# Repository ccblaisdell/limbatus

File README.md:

# limbatus

A 36-key wireless monoblock ergonomic keyboard derived from Dimetrodon.

## Current status
- Ships as a **36-key** layout (3 thumb keys per side).
- Matrix is organized as a XIAO BLE-compatible logical `6 x 6` scan.
- `NFC1` is reserved for matrix use and must be configured as GPIO in firmware.
- The thumb cluster's anchor/shift/splay values match Dimetrodon's thumb
  cluster exactly (same fan shape, ported into limbatus's mirrored monoblock
  frame).

## Latest PCB Images
- Top view: https://ccblaisdell.github.io/limbatus/limbatus-top.png
- Bottom view: https://ccblaisdell.github.io/limbatus/limbatus-bottom.png

## Build
1. Install dependencies:
   - `npm install`
2. Generate artifacts:
   - `make build`

For hand-assembly (soldering and case), see [`BUILD.md`](BUILD.md). Parts list is in [`BOM.md`](BOM.md).

## Firmware
Runs [ZMK](https://zmk.dev) as a single (non-split) XIAO BLE image. The config,
keymaps, pin map, and build/flash notes live in [`config/`](config/README.md);
CI builds the `limbatus` shield and uploads a `.uf2` artifact.

Default keymap (rendered by [keymap-drawer](https://github.com/caksoylar/keymap-drawer)):

## Verify Ergogen Changes
Run this whenever you change `ergogen/config.yaml`.

1. Build:
   - `make build`
2. Verify generated artifacts exist:
   - `ls outlines`
   - `ls pcbs`
3. Check what changed:
   - `git status --short`
4. In KiCad, open the generated board and confirm:
   - no missing footprints
   - 36 keys present
   - MCU footprint placement still valid
   - no obvious overlap/regression in thumb cluster or center bridge

## Keyboard References
- https://github.com/ceoloide/corney-island for its GitHub Actions and workflows.
- https://github.com/ccblaisdell/dimetrodon for your previous keyboard iteration.

## Notes
- Target MCU is XIAO BLE nRF52840.
- Matrix pin map target: `P0..P5` for columns, `P6..P10` plus `NFC1` for rows.
- Includes a dedicated power switch footprint.
- No JST footprint; battery uses two direct-solder SMD pads (`local/battery_pads_solder`).
- No external reset switch footprint; rely on the onboard XIAO reset button.
- The current code-generated case approach is documented in `case/README.md` and is intended to use Ergogen DXFs plus an OpenSCAD/FreeCAD export flow.

## TODO
- Add 3d models for parts where possible
- Implement the code-generated case plan in `case/README.md`
- Design a second case with embedded apple magic trackpad

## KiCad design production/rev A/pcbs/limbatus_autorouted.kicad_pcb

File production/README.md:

# Production artifacts

This directory holds **production bundles**: frozen snapshots of the exact
fabrication artifacts for a specific board revision — the gerbers you actually
order, together with the PCB and outlines they were generated from.

Everything else generated by Ergogen (`outlines/`, `pcbs/`) and by KiBot
(root `gerbers/`) is a **live build product** and is intentionally *not* committed
(see `.gitignore`). `ergogen/config.yaml` is the single source of truth; run
`make build` (or download the CI build artifacts) to regenerate the current
design at any time.

## Layout

```
production/
  rev <version>/                 # e.g. 2026-08-01-jlcpcb
    gerbers/
      limbatus/               # base-board gerbers
      limbatus.zip            # the zip actually uploaded to the fab
      limbatus_autorouted/    # autorouted-board gerbers (if used)
      limbatus_autorouted.zip
    limbatus.kicad_pcb        # the exact PCB the gerbers came from
    outlines/                 # matching board/case outlines
    BOM.csv                   # optional: BOM as ordered
    SOURCE.md                 # provenance: source commit, date, fab, order id
```

A bundle is **immutable** once committed. It is guaranteed internally consistent
(gerbers ⇄ PCB ⇄ outlines all from one build), which is the property root-level
live outputs cannot promise as the design evolves.

## Cutting a new production bundle

Bundles are created and committed **by hand** — nothing in CI writes here.
When you are ready to place an order:

1. Regenerate from the commit you intend to fab: `make build`, then run the
   KiBot/autoroute steps to produce `gerbers/` (or pull them from the `Build`
   workflow's `kibot-default` artifact for that commit).
2. Copy the artifacts into `production/<order-id>/`:
   - `gerbers/`            → `production/<order-id>/gerbers/`
   - `pcbs/limbatus.kicad_pcb` → `production/<order-id>/limbatus.kicad_pcb`
   - `outlines/`          → `production/<order-id>/outlines/`
3. Write `production/<order-id>/SOURCE.md` recording the source commit, date,
   fab, and order id (copy an existing bundle's `SOURCE.md` as a template).
4. Commit the bundle and tag it: `git tag fab-<order-id> && git push --tags`.

Because `outlines/`, `pcbs/`, and root `gerbers/` are gitignored, use
`git add -f production/<order-id>` — the `production/` path itself is not
ignored, so a normal `git add production/<order-id>` works too.

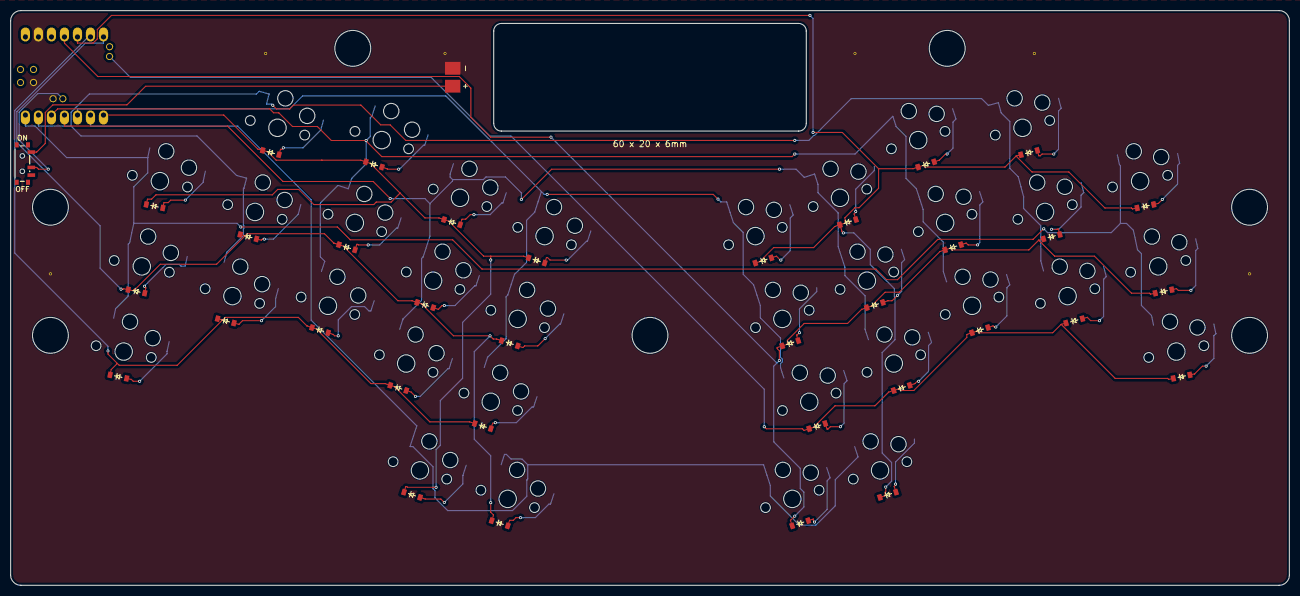
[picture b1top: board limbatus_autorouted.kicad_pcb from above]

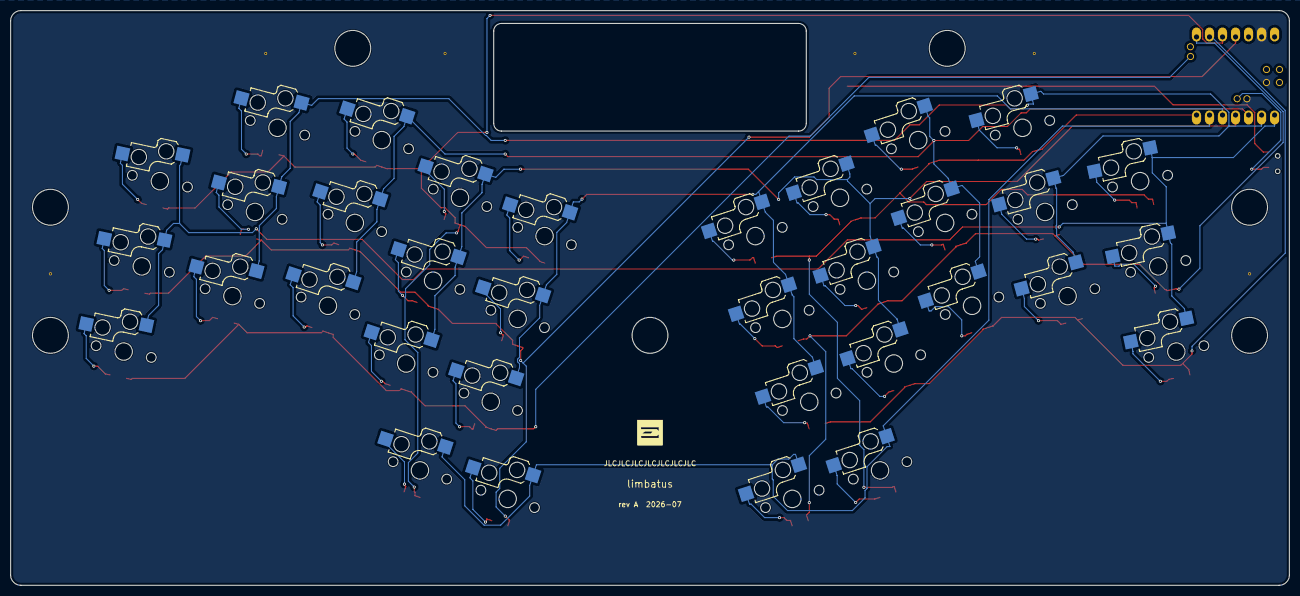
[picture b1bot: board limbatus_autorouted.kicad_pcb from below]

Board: 2 copper layers, 249.5 x 112.1 mm, 85 parts (35 on the bottom side), 49 nets.

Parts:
BAT1: battery_pads_solder
D1, D2, D3, D4, D5, D6, D7, D8, D9, D10, D11, D12, D13, D14, D15, D16, D17, D18, D19, D20, D21, D22, D23, D24, D25, D26, D27, D28, D29, D30, D31, D32, D33, D34: diode_tht_sod123
LOGO1: utility_ergogen_logo
MCU1: XIAO-BLE
MH1, MH2, MH3, MH4, MH5, MH6, MH7: mounting_hole_npth
PWR1: power_switch_smd_side
S1, S2, S3, S4, S5, S6, S7, S8, S9, S10, S11, S12, S13, S14, S15, S16, S17, S18, S19, S20, S21, S22, S23, S24, S25, S26, S27, S28, S29, S30, S31, S32, S33, S34: switch_choc_v1_v2
V1, V2, V3, V4, V5, V6: stitching_via

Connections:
Braw: BAT1.1, PWR1.1
C0: MCU1.1, S1.1, S2.1, S3.1, S18.1, S19.1, S20.1
C1: MCU1.2, S4.1, S5.1, S6.1, S21.1, S22.1, S23.1
C2: MCU1.3, S7.1, S8.1, S9.1, S24.1, S25.1, S26.1
C3: MCU1.4, S10.1, S11.1, S12.1, S27.1, S28.1, S29.1
C4: MCU1.5, S13.1, S14.1, S15.1, S30.1, S31.1, S32.1
C5: MCU1.6, S16.1, S17.1, S33.1, S34.1
GND: BAT1.2, MCU1.13, MCU1.17, MCU1.20, V1.1, V2.1, V3.1, V4.1, V5.1, V6.1
R0: D3.1, D6.1, D9.1, D12.1, D15.1, D16.1, MCU1.7
R1: D2.1, D5.1, D8.1, D11.1, D14.1, D17.1, MCU1.8
R2: D1.1, D4.1, D7.1, D10.1, D13.1, MCU1.9
R3: D20.1, D23.1, D26.1, D29.1, D32.1, D33.1, MCU1.10
R4: D19.1, D22.1, D25.1, D28.1, D31.1, D34.1, MCU1.11
R5: D18.1, D21.1, D24.1, D27.1, D30.1, MCU1.21
RAW: MCU1.19, PWR1.2
SW_left_matrix_inner_bottom: D13.2, S13.2
SW_left_matrix_inner_home: D14.2, S14.2
SW_left_matrix_inner_top: D15.2, S15.2
SW_left_matrix_middle_bottom: D7.2, S7.2
SW_left_matrix_middle_home: D8.2, S8.2
SW_left_matrix_middle_top: D9.2, S9.2
SW_left_matrix_pinky_bottom: D1.2, S1.2
SW_left_matrix_pinky_home: D2.2, S2.2
SW_left_matrix_pinky_top: D3.2, S3.2
SW_left_matrix_pointer_bottom: D10.2, S10.2
SW_left_matrix_pointer_home: D11.2, S11.2
SW_left_matrix_pointer_top: D12.2, S12.2
SW_left_matrix_ring_bottom: D4.2, S4.2
SW_left_matrix_ring_home: D5.2, S5.2
SW_left_matrix_ring_top: D6.2, S6.2
SW_left_thumbs_middle_cluster: D17.2, S17.2
SW_left_thumbs_tucky_cluster: D16.2, S16.2
SW_mirror_left_matrix_inner_bottom: D30.2, S30.2
SW_mirror_left_matrix_inner_home: D31.2, S31.2
SW_mirror_left_matrix_inner_top: D32.2, S32.2
SW_mirror_left_matrix_middle_bottom: D24.2, S24.2
SW_mirror_left_matrix_middle_home: D25.2, S25.2
SW_mirror_left_matrix_middle_top: D26.2, S26.2
SW_mirror_left_matrix_pinky_bottom: D18.2, S18.2
SW_mirror_left_matrix_pinky_home: D19.2, S19.2
SW_mirror_left_matrix_pinky_top: D20.2, S20.2
SW_mirror_left_matrix_pointer_bottom: D27.2, S27.2
SW_mirror_left_matrix_pointer_home: D28.2, S28.2
SW_mirror_left_matrix_pointer_top: D29.2, S29.2
SW_mirror_left_matrix_ring_bottom: D21.2, S21.2
SW_mirror_left_matrix_ring_home: D22.2, S22.2
SW_mirror_left_matrix_ring_top: D23.2, S23.2
SW_mirror_left_thumbs_middle_cluster: D34.2, S34.2
SW_mirror_left_thumbs_tucky_cluster: D33.2, S33.2

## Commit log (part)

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2026-03-02 Add agents config
2026-03-02 Generated an ergogen config
2026-03-02 Set node version
2026-03-02 Initial npm install
2026-03-02 Verification instructions
2026-03-02 Fix skip option error
2026-03-02 Fix mirroring
2026-03-02 Fix spacing
2026-03-02 Rotation, spacing, and remove arc from thumbs
2026-03-02 Fixed rectangular board
2026-03-03 Remove reset button
2026-03-03 Move controller to the board edge
2026-03-03 Remove references to rp2040
2026-03-04 Use ceoloide's choc switch footprint
2026-03-05 Add ceoloide's footprints as git submodule
2026-03-05 Add actual xiao footprint
2026-03-05 Add github workflow
2026-03-05 Add reproducibility check to CI workflow
2026-03-05 Port KiBot action wrappers and add CI KiBot job
2026-03-05 Make KiBot action compatible with generated PCB token
2026-03-05 Deploy KiBot images to GitHub Pages
2026-03-05 Enable Pages setup during workflow deploy
2026-03-05 Grant Pages permissions to KiBot job
2026-03-05 Gate Pages deploy behind ENABLE_PAGES variable
2026-03-05 Run Pages deploy on main without feature flag
2026-03-05 Fix yaml unhappiness
2026-03-05 Add TODOS to readme
2026-03-07 Add published PCB images to README
2026-03-08 Add dimetrodon power switch footprint to Ergogen config
2026-03-08 Bring halves closer together
2026-03-08 Update readme with reference implementations
2026-03-08 Wire DSN autoroute pipeline into CI and update TODOs
2026-03-08 Use default KiBot config for autorouted board outputs
2026-03-09 Add top-side 20x32 battery placement scaffold
2026-03-09 Move xiao to the corner, bigger battery
2026-03-10 Tweak outlines
2026-03-10 Add SMD diodes
2026-03-10 Add case plan, will follow up on it later
2026-03-11 Reference local corney-island repo
2026-03-11 Use NFC1 pin for 6x6 matrix
2026-03-11 Move diodes
2026-03-11 Tweak diode placement a little more
2026-03-11 Prep for the case
2026-03-12 Switch from codex to claude
2026-03-12 Added outlines intended to help with the case
2026-03-14 First pass at a case
2026-06-10 Trying to iterate on the openscad case
2026-06-25 Ignore worktrees
2026-06-27 Raise inner thumb a little
2026-06-29 Tweak battery position and size
2026-06-30 Claude permission changes
